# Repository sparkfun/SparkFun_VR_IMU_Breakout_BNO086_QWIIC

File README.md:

SparkFun VR IMU Breakout - BNO086 (Qwiic)
========================================

[*SparkFun VR IMU Breakout - BNO086 (Qwiic)(SEN-22857)*](https://www.sparkfun.com/products/22857)

The BNO086 IMU has a combination triple axis accelerometer/gyro/magnetometer packaged with an ARM Cortex M0+ running powerful algorithms.

Repository Contents
-------------------

* **/Documentation** - Datasheets, additional product information
* **/Hardware** - Eagle design files (.brd, .sch)
  * **/Production** - Production panel files (.brd)

Documentation
--------------
* **[Library](https://github.com/sparkfun/SparkFun_BNO08x_Arduino_Library)** - Arduino library for the BNO086 and variants BNO08X.
* **[Fritzing Part](https://github.com/sparkfun/Fritzing_Parts/blob/main/products/22857-sfe_vr_imu_breakout_bno086_9dof_accelerometer_gyro_magnetometer.fzpz)**
* **[Hookup Guide](https://docs.sparkfun.com/SparkFun_VR_IMU_Breakout_BNO086_QWIIC/introduction/)** - Basic hookup guide for the SparkFun VR IMU Breakout - BNO086.

Product Versions
----------------
* [SEN-22857](https://www.sparkfun.com/products/22857) - Initial release, v1.0

Version History
---------------
* v1.0 - Initial release

License Information
-------------------

This product is _**open source**_!

Please review the LICENSE.md file for license information.

If you have any questions or concerns on licensing, please contact technical support on our [SparkFun forums](https://forum.sparkfun.com/viewforum.php?f=152).

Distributed as-is; no warranty is given.

- Your friends at SparkFun.

_<COLLABORATION CREDIT>_

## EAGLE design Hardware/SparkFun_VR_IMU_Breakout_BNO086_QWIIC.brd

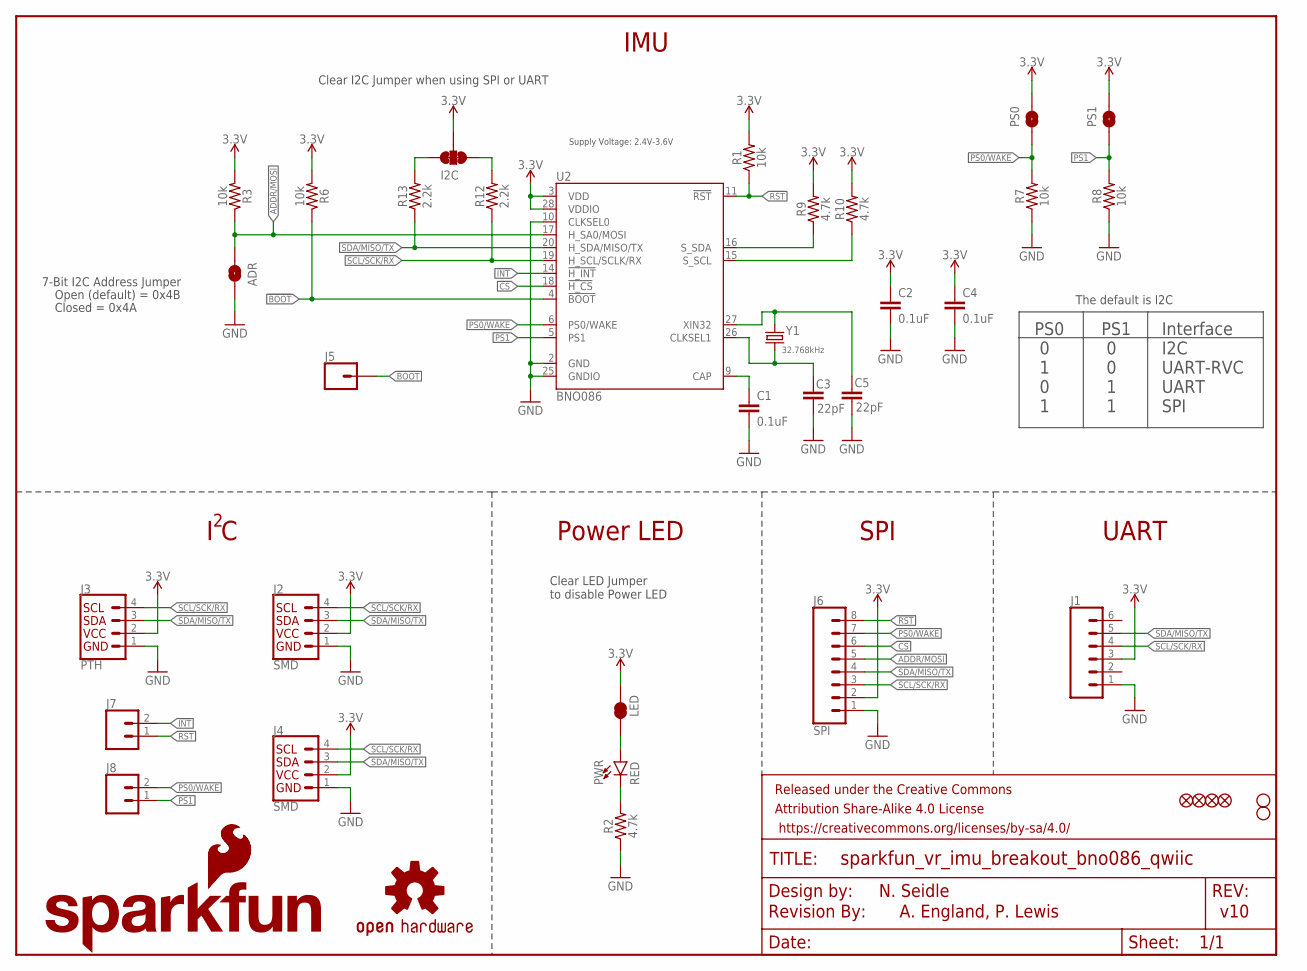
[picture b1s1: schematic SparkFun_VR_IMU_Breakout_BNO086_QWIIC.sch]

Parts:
ADR: JUMPER-SMT_2_NO_SILK; SMT-JUMPER_2_NO_SILK
C1, C2, C4: 0.1uF; 0603
C3, C5: 22pF; 0603
FRAME1: FRAME-LETTER; CREATIVE_COMMONS
I2C: JUMPER-SMT_3_2-NC_TRACE_SILK; SMT-JUMPER_3_2-NC_TRACE_SILK
J1: CONN_06NO_SILK_FEMALE_PTH; 1X06_NO_SILK
J2, J4: SMD; JST04_1MM_RA
J3: PTH; 1X04_NO_SILK
J5: CONN_01PTH_NO_SILK_YES_STOP; 1X01_NO_SILK
J6: SPI; 1X08_NO_SILK
J7, J8: CONN_021X02_NO_SILK; 1X02_NO_SILK
JP1, JP2, JP5, JP6: FIDUCIALUFIDUCIAL; FIDUCIAL-MICRO
JP3, JP4: STAND-OFF
LED: JUMPER-SMT_2_NC_TRACE_SILK; SMT-JUMPER_2_NC_TRACE_SILK
LOGO1: OSHW-LOGOMINI; OSHW-LOGO-MINI
LOGO2: REVISION
LOGO4: SFE_LOGO_FLAME.2_INCH; SFE_LOGO_FLAME_.2
LOGO5: SFE_LOGO_NAME_FLAME.1_INCH; SFE_LOGO_NAME_FLAME_.1
PS0, PS1: JUMPER-SMT_2_NO_SILK; SMT-JUMPER_2_NO_SILK
PWR: RED; LED-0603
R1, R3, R6, R7, R8: 10k; 0603
R2, R9, R10: 4.7k; 0603
R12, R13: 2.2k; 0603
U2: BNO086; LGA-28
Y1: 32.768kHz; CRYSTAL-SMD-3.2X1.5MM

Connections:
3.3V: C2.1, C4.1, I2C.2, J1.3, J2.2, J3.2, J4.2, J6.2, LED.1, PS0.1, PS1.1, R1.2, R3.2, R6.2, R9.2, R10.2, U2.3 (VDD), U2.28 (VDDIO)
!BOOT: J5.1, R6.1, U2.4 (!BOOT)
!CS: J6.6, U2.18 (!H_CS)
!INT: J7.2, U2.14 (!H_INT)
!RST: J6.8, J7.1, R1.1, U2.11 (!RST)
ADDR/MOSI: ADR.2, J6.5, R3.1, U2.17 (H_SA0/MOSI)
CAP: C1.1, U2.9 (CAP)
GND: ADR.1, C1.2, C2.2, C3.2, C4.2, C5.2, J1.1, J2.1, J3.1, J4.1, J6.1, R2.1, R7.1, R8.1, U2.2 (GND), U2.10 (CLKSEL0), U2.25 (GNDIO)
unnamed: C5.1, U2.27 (XIN32), Y1.P$2 (2)
unnamed: C3.1, U2.26 (CLKSEL1), Y1.P$1 (1)
unnamed: PWR.C, R2.2
unnamed: LED.2, PWR.A
PS0/WAKE: J6.7, J8.2, PS0.2, R7.2, U2.6 (PS0/WAKE)
PS1: J8.1, PS1.2, R8.2, U2.5 (PS1)
SCL/SCK/RX: J1.4, J2.4, J3.4, J4.4, J6.3, R12.1, U2.19 (H_SCL/SCLK/RX)
SCL_PU: I2C.1, R12.2
SDA/MISO/TX: J1.5, J2.3, J3.3, J4.3, J6.4, R13.1, U2.20 (H_SDA/MISO/TX)
SDA_PU: I2C.3, R13.2
S_SCL: R10.1, U2.15 (S_SCL)
S_SDA: R9.1, U2.16 (S_SDA)

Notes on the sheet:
N. Seidle
v10
7-Bit I2C Address Jumper
Closed = 0x4A
Open (default) = 0x4B
PS0 0 1 0 1
PS1 0 0 1 1
Interface I2C UART-RVC UART SPI
The default is I2C
Clear I2C Jumper when using SPI or UART
I C
UART
SPI
A. England, P. Lewis
Supply Voltage: 2.4V-3.6V
IMU
Clear LED Jumper to disable Power LED
Power LED

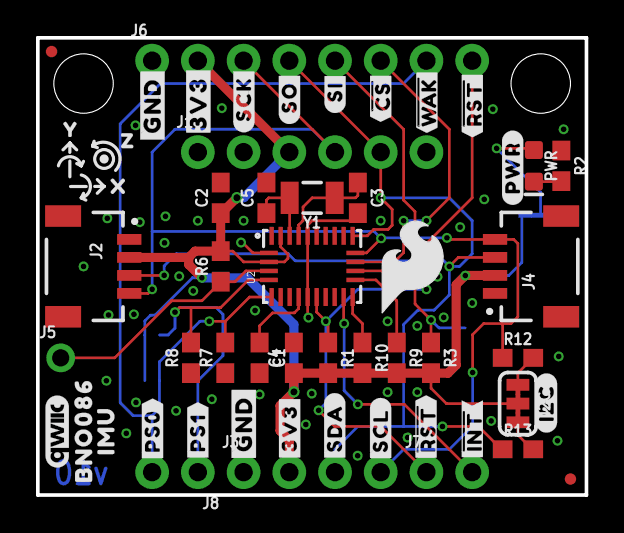
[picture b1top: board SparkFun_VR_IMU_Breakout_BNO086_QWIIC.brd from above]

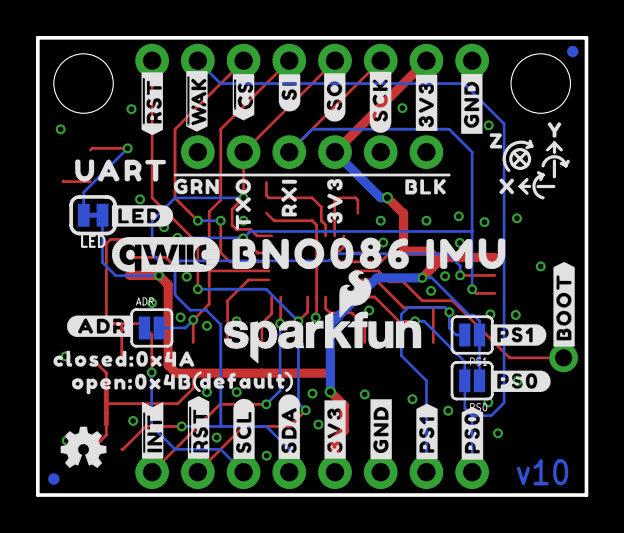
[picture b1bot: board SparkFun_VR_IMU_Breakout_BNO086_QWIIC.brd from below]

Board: 2 copper layers, 30.5 x 25.4 mm, 102 parts (43 on the bottom side), 20 nets.

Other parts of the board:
U$1: #I2C#874
U$2: BLK889
U$3, U$25: X878
U$4: ##INT##6
U$5: ##RST##5
U$6, U$10: Y879
U$7, U$15: Z880
U$8: #SCL#4
U$9, U$16: #GND#2
U$11: #SCK#882
U$12: #SO#867
U$13: #SI#868
U$14: #SDA#3
U$17: ##CS##870
U$18: ##CS##885
U$19: ##RST##872
U$20: ##RST##887
U$21: RXI891
U$22: TXO892
U$23: #PS0#874
U$24: BNO0861
U$26: #LED#0
U$27, U$46: #3V3#874
U$28: OPEN#0X4B0
U$29: QWIIC_4MM
U$30: #ADR#894
U$31: IMU862
U$32, U$45: #GND#864
U$33: #PS1#1
U$34: #PS0#2
U$35: #PS1#895
U$36: #3V3#865
U$37: #SCK#866
U$38: ##WAK##871
U$39: #3V3#882
U$40: 3V3891
U$41: GRN890
U$42: #PWR#873
U$43: #PS1#874
U$44: UART881
U$47: #SDA#874
U$48: #SCL#875
U$49: #BOOT#888
U$50: ##RST##876
U$51: ##INT##877
U$52: QWIIC_6MM
U$53: ##WAK##886
U$54: BNO086_IMU881
U$55: #SO#883
U$56: #SI#884
U$57: #PS0#895
U$58: CLOSED#0X4A0
U$59: ORDERING_INSTRUCTIONS
U$61: DEFAULT0

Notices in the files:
parts and their libraries:
SparkFun-Resistors: Licensing: Creative Commons ShareAlike 4.0 International - https://creativecommons.org/licenses/by-sa/4.0
SparkFun-Aesthetics: Released under the Creative Commons Attribution Share-Alike 4.0 License
SparkFun-Aesthetics: https://creativecommons.org/licenses/by-sa/4.0
